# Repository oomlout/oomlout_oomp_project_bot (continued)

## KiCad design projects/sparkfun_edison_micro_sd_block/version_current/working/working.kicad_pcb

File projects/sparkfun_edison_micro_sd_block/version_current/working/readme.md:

# Edison_Micro_SD_Block by sparkfun  
This is a harvested standardized copy of a project from github.  
The original project can be found at:  
https://github.com/sparkfun/Edison_Micro_SD_Block  
Please consult that link for additional, details, files, and license information.  
Note: It was auto harvested and if the original repo had more than one board file or anything out of the ordinary the files here are likely not representative.

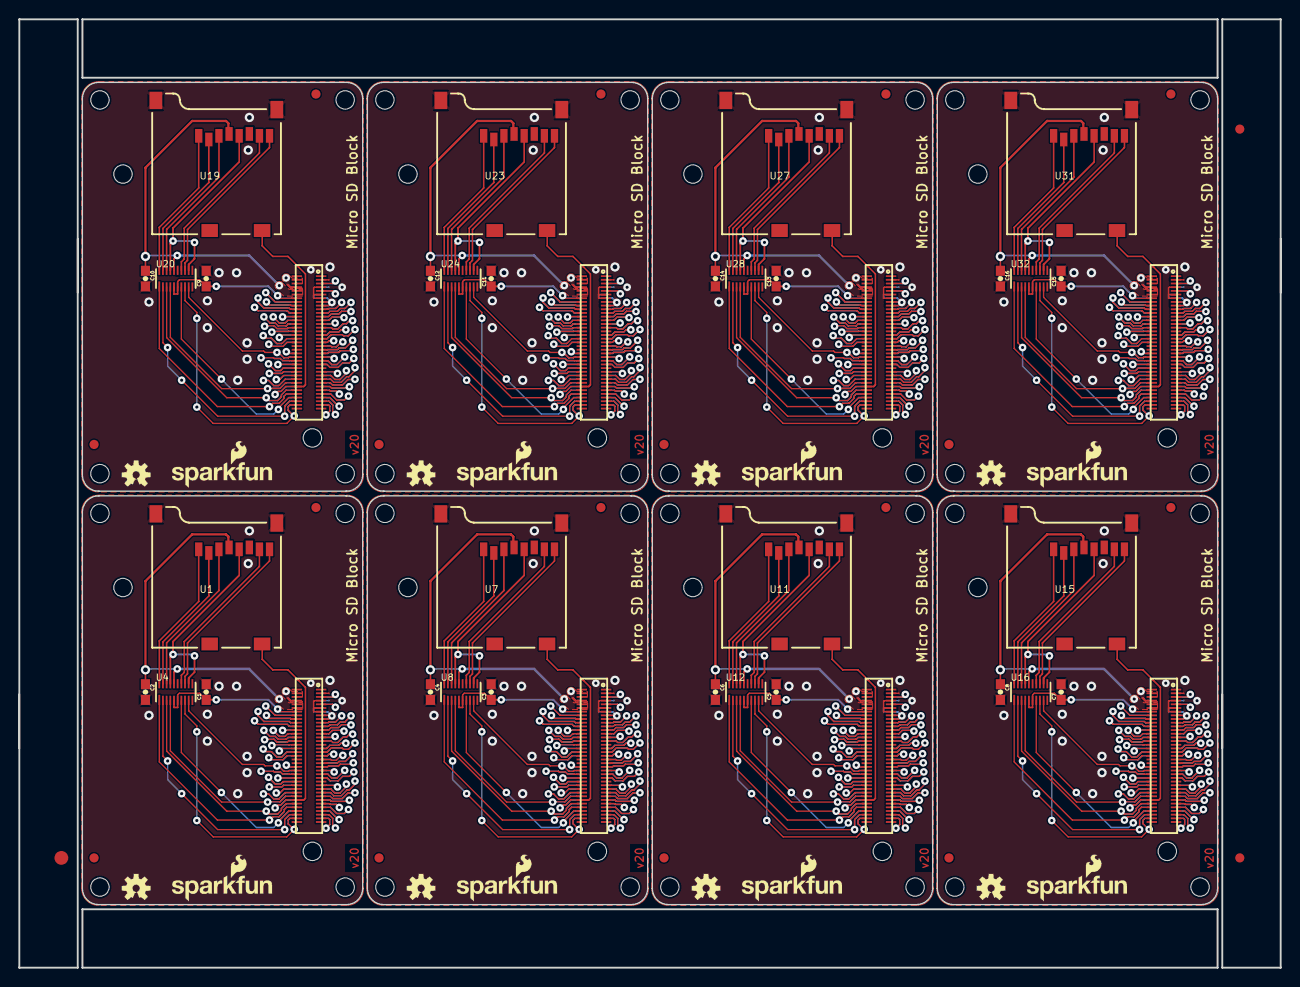
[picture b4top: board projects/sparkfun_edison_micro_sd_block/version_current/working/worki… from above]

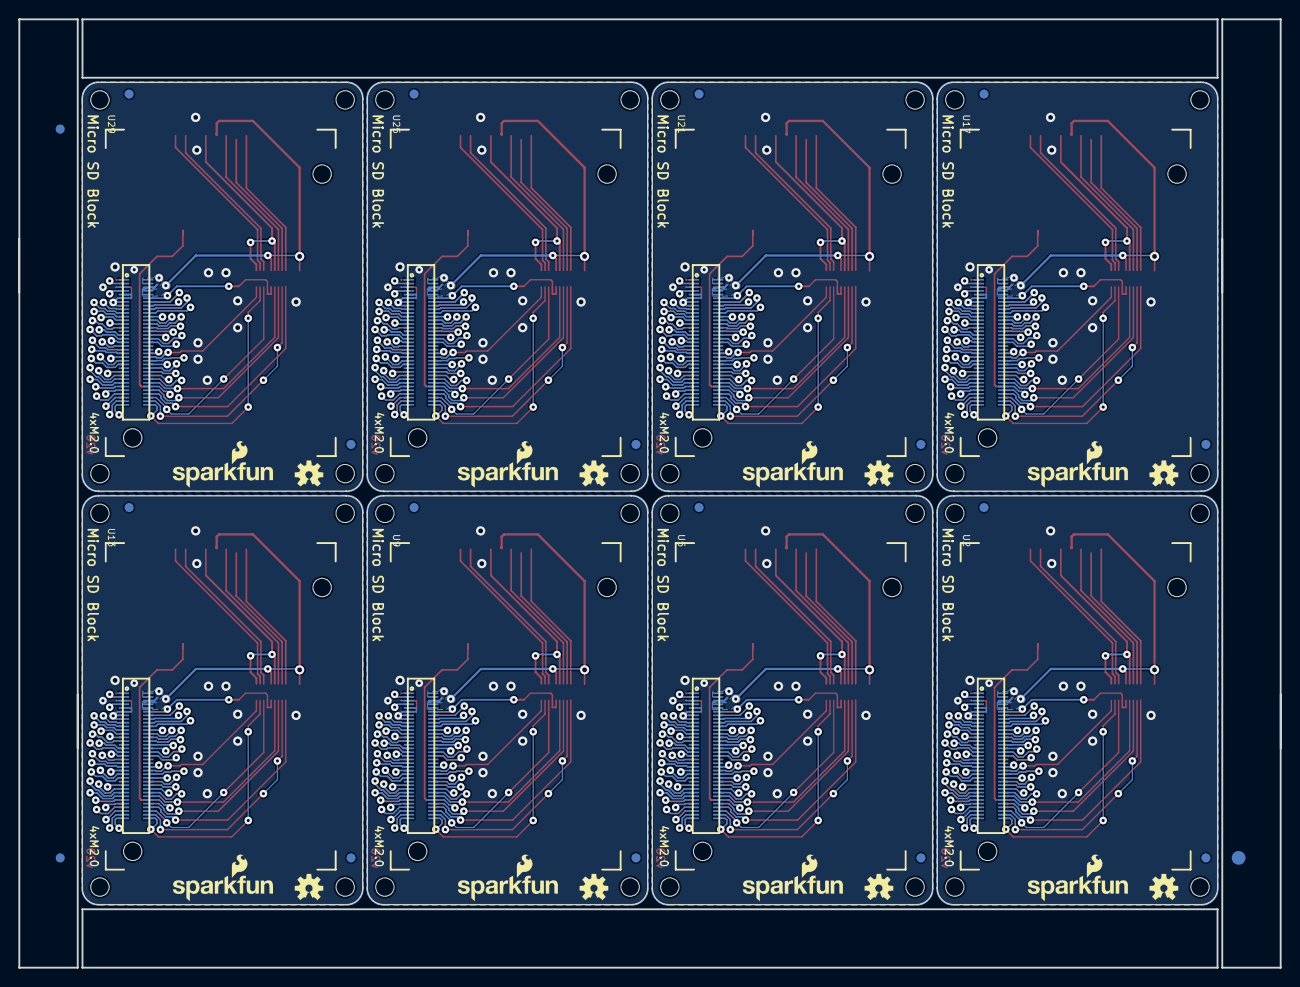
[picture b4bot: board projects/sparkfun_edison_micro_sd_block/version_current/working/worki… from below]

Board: 4 copper layers, 137.2 x 103.1 mm, 150 parts (51 on the bottom side), 512 nets.

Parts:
@HOLE0, @HOLE1, @HOLE2, @HOLE3, @HOLE4, @HOLE5, @HOLE6, @HOLE7, @HOLE8, @HOLE9, @HOLE10, @HOLE11, @HOLE12, @HOLE13, @HOLE14, @HOLE15, @HOLE16, @HOLE17, @HOLE18, @HOLE19, @HOLE20, @HOLE21, @HOLE22, @HOLE23, @HOLE24, @HOLE25, @HOLE26, @HOLE27, @HOLE28, @HOLE29, @HOLE30, @HOLE31: (no value)
C1, C2, C3, C4, C5, C6, C7, C8, C9, C10, C11, C12, C13, C14, C15, C16: 0.1uF; 0603-CAP
E$1, E$2: FIDUCIAL-1.5X3
E$3, E$4, E$5, E$6: FIDUCIAL-1X2
FID1, FID2, FID3, FID4, FID5, FID6, FID7, FID8, FID9, FID10, FID11, FID12, FID13, FID14, FID15, FID16, FID17, FID18, FID19, FID20, FID21, FID22, FID23, FID24, FID25, FID26, FID27, FID28, FID29, FID30, FID31, FID32: FIDUCIAL1X2; FIDUCIAL-1X2
LOGO1, LOGO2, LOGO5, LOGO7, LOGO9, LOGO11, LOGO13, LOGO15, LOGO17, LOGO19, LOGO21, LOGO23, LOGO25, LOGO27, LOGO29, LOGO31: OSHW-LOGOS; OSHW-LOGO-S
LOGO3, LOGO4, LOGO6, LOGO8, LOGO10, LOGO12, LOGO14, LOGO16, LOGO18, LOGO20, LOGO22, LOGO24, LOGO26, LOGO28, LOGO30, LOGO32: SFE_LOGO_NAME_FLAME.1_INCH; SFE_LOGO_NAME_FLAME_.1
U1, U7, U11, U15, U19, U23, U27, U31: USD-SOCKETNEW; MICRO-SD-SOCKET-PP
U2, U5, U9, U13, U17, U21, U25, U29: EDISON_CONNECTOR_FULLMOUNTING_HOLES; EDISON_DAUGHTER
U3, U6, U10, U14, U18, U22, U26, U30: EDISON_CONNECTOR_FULLHEADER; DF40C-70DP-0.4(51)
U4, U8, U12, U16, U20, U24, U28, U32: TXB0108; UFDFN-20

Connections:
1.8V: C1.1, U2.12, U3.12, U4.P$5, U4.P$6
1.8V1: C3.1, U5.12, U6.12, U8.P$5, U8.P$6
1.8V2: C5.1, U9.12, U10.12, U12.P$5, U12.P$6
1.8V3: C7.1, U13.12, U14.12, U16.P$5, U16.P$6
1.8V4: C9.1, U17.12, U18.12, U20.P$5, U20.P$6
1.8V5: C11.1, U21.12, U22.12, U24.P$5, U24.P$6
1.8V6: C13.1, U25.12, U26.12, U28.P$5, U28.P$6
1.8V7: C15.1, U29.12, U30.12, U32.P$5, U32.P$6
3.3V: C2.1, U1.4, U2.8, U2.10, U3.8, U3.10, U4.P$16
3.3V1: C4.1, U5.8, U5.10, U6.8, U6.10, U7.4, U8.P$16
3.3V2: C6.1, U9.8, U9.10, U10.8, U10.10, U11.4, U12.P$16
3.3V3: C8.1, U13.8, U13.10, U14.8, U14.10, U15.4, U16.P$16
3.3V4: C10.1, U17.8, U17.10, U18.8, U18.10, U19.4, U20.P$16
3.3V5: C12.1, U21.8, U21.10, U22.8, U22.10, U23.4, U24.P$16
3.3V6: C14.1, U25.8, U25.10, U26.8, U26.10, U27.4, U28.P$16
3.3V7: C16.1, U29.8, U29.10, U30.8, U30.10, U31.4, U32.P$16
DCIN: U2.14, U3.14
DCIN1: U5.14, U6.14
DCIN2: U9.14, U10.14
DCIN3: U13.14, U14.14
DCIN4: U17.14, U18.14
DCIN5: U21.14, U22.14
DCIN6: U25.14, U26.14
DCIN7: U29.14, U30.14
FAULT: U2.19, U3.19
FAULT1: U5.19, U6.19
FAULT2: U9.19, U10.19
FAULT3: U13.19, U14.19
FAULT4: U17.19, U18.19
FAULT5: U21.19, U22.19
FAULT6: U25.19, U26.19
FAULT7: U29.19, U30.19
FW_RCVR: U2.69, U3.69
FW_RCVR1: U5.69, U6.69
FW_RCVR2: U9.69, U10.69
FW_RCVR3: U13.69, U14.69
FW_RCVR4: U17.69, U18.69
FW_RCVR5: U21.69, U22.69
FW_RCVR6: U25.69, U26.69
FW_RCVR7: U29.69, U30.69
GND: C1.2, C2.2, U1.6, U1.GND1, U1.GND3, U2.1, U2.5, U2.9, U2.11, U2.13, U2.15, U3.1, U3.5, U3.9, U3.11, U3.13, U3.15, U4.P$15
GND1: C3.2, C4.2, U5.1, U5.5, U5.9, U5.11, U5.13, U5.15, U6.1, U6.5, U6.9, U6.11, U6.13, U6.15, U7.6, U7.GND1, U7.GND3, U8.P$15
GND2: C5.2, C6.2, U9.1, U9.5, U9.9, U9.11, U9.13, U9.15, U10.1, U10.5, U10.9, U10.11, U10.13, U10.15, U11.6, U11.GND1, U11.GND3, U12.P$15
GND3: C7.2, C8.2, U13.1, U13.5, U13.9, U13.11, U13.13, U13.15, U14.1, U14.5, U14.9, U14.11, U14.13, U14.15, U15.6, U15.GND1, U15.GND3, U16.P$15
GND4: C9.2, C10.2, U17.1, U17.5, U17.9, U17.11, U17.13, U17.15, U18.1, U18.5, U18.9, U18.11, U18.13, U18.15, U19.6, U19.GND1, U19.GND3, U20.P$15
GND5: C11.2, C12.2, U21.1, U21.5, U21.9, U21.11, U21.13, U21.15, U22.1, U22.5, U22.9, U22.11, U22.13, U22.15, U23.6, U23.GND1, U23.GND3, U24.P$15
GND6: C13.2, C14.2, U25.1, U25.5, U25.9, U25.11, U25.13, U25.15, U26.1, U26.5, U26.9, U26.11, U26.13, U26.15, U27.6, U27.GND1, U27.GND3, U28.P$15
GND7: C15.2, C16.2, U29.1, U29.5, U29.9, U29.11, U29.13, U29.15, U30.1, U30.5, U30.9, U30.11, U30.13, U30.15, U31.6, U31.GND1, U31.GND3, U32.P$15
GP1: U5.48, U6.48
GP2: U5.42, U6.42
GP3: U5.34, U6.34
GP4: U5.32, U6.32
GP5: U5.30, U6.30
GP6: U5.28, U6.28
GP7: U5.26, U6.26
GP8: U5.25, U6.25
GP9: U5.24, U6.24
GP10: U9.48, U10.48
GP11: U9.42, U10.42
GP12: U9.34, U10.34
GP12_PWM0: U2.35, U3.35
GP12_PWM1: U5.35, U6.35
GP12_PWM2: U9.35, U10.35
GP12_PWM3: U13.35, U14.35
GP12_PWM4: U17.35, U18.35
GP12_PWM5: U21.35, U22.35
GP12_PWM6: U25.35, U26.35
GP12_PWM7: U29.35, U30.35
GP13: U9.32, U10.32
GP13_PWM1: U2.33, U3.33
GP13_PWM2: U5.33, U6.33
GP13_PWM3: U9.33, U10.33
GP13_PWM4: U13.33, U14.33
GP13_PWM5: U17.33, U18.33
GP13_PWM6: U21.33, U22.33
GP13_PWM7: U25.33, U26.33
GP13_PWM8: U29.33, U30.33
GP14: U2.48, U3.48
GP15: U2.42, U3.42
GP16: U9.30, U10.30
GP17: U9.28, U10.28
GP18: U9.26, U10.26
GP19: U9.25, U10.25
GP19_I2C_1_SCL: U2.41, U3.41
GP19_I2C_1_SCL1: U5.41, U6.41
GP19_I2C_1_SCL2: U9.41, U10.41
GP19_I2C_1_SCL3: U13.41, U14.41
GP19_I2C_1_SCL4: U17.41, U18.41
GP19_I2C_1_SCL5: U21.41, U22.41
GP19_I2C_1_SCL6: U25.41, U26.41
GP19_I2C_1_SCL7: U29.41, U30.41
GP20: U9.24, U10.24
GP20_I2C_1_SDA: U2.43, U3.43
GP20_I2C_1_SDA1: U5.43, U6.43
GP20_I2C_1_SDA2: U9.43, U10.43
GP20_I2C_1_SDA3: U13.43, U14.43
GP20_I2C_1_SDA4: U17.43, U18.43
GP20_I2C_1_SDA5: U21.43, U22.43
GP20_I2C_1_SDA6: U25.43, U26.43
GP20_I2C_1_SDA7: U29.43, U30.43
GP21: U13.48, U14.48
GP22: U13.42, U14.42
GP23: U13.34, U14.34
GP24: U13.32, U14.32
GP25: U13.30, U14.30
GP26: U13.28, U14.28
GP27: U13.26, U14.26
GP27_I2C_6_SCL: U2.45, U3.45
GP27_I2C_6_SCL1: U5.45, U6.45
GP27_I2C_6_SCL2: U9.45, U10.45
GP27_I2C_6_SCL3: U13.45, U14.45
GP27_I2C_6_SCL4: U17.45, U18.45
GP27_I2C_6_SCL5: U21.45, U22.45
GP27_I2C_6_SCL6: U25.45, U26.45
GP27_I2C_6_SCL7: U29.45, U30.45
GP28: U13.25, U14.25
GP28_I2C_6_SDA: U2.47, U3.47
GP28_I2C_6_SDA1: U5.47, U6.47
GP28_I2C_6_SDA2: U9.47, U10.47
GP28_I2C_6_SDA3: U13.47, U14.47
GP28_I2C_6_SDA4: U17.47, U18.47
GP28_I2C_6_SDA5: U21.47, U22.47
GP28_I2C_6_SDA6: U25.47, U26.47
GP28_I2C_6_SDA7: U29.47, U30.47
GP29: U13.24, U14.24
GP30: U17.48, U18.48
GP31: U17.42, U18.42
GP32: U17.34, U18.34
GP33: U17.32, U18.32
GP34: U17.30, U18.30
GP35: U17.28, U18.28
GP36: U17.26, U18.26
GP37: U17.25, U18.25
GP38: U17.24, U18.24
GP39: U21.48, U22.48
GP40: U21.42, U22.42
GP40_I2S_2_CLK: U2.52, U3.52
GP40_I2S_2_CLK1: U5.52, U6.52
GP40_I2S_2_CLK2: U9.52, U10.52
GP40_I2S_2_CLK3: U13.52, U14.52
GP40_I2S_2_CLK4: U17.52, U18.52
GP40_I2S_2_CLK5: U21.52, U22.52
GP40_I2S_2_CLK6: U25.52, U26.52
GP40_I2S_2_CLK7: U29.52, U30.52
GP41: U21.34, U22.34
GP41_I2S_2_FS: U2.54, U3.54
GP41_I2S_2_FS1: U5.54, U6.54
GP41_I2S_2_FS2: U9.54, U10.54
GP41_I2S_2_FS3: U13.54, U14.54
GP41_I2S_2_FS4: U17.54, U18.54
GP41_I2S_2_FS5: U21.54, U22.54
GP41_I2S_2_FS6: U25.54, U26.54
GP41_I2S_2_FS7: U29.54, U30.54
GP42: U21.32, U22.32
GP42_I2S_2_RXD: U2.50, U3.50
GP42_I2S_2_RXD1: U5.50, U6.50
GP42_I2S_2_RXD2: U9.50, U10.50
GP42_I2S_2_RXD3: U13.50, U14.50
GP42_I2S_2_RXD4: U17.50, U18.50
GP42_I2S_2_RXD5: U21.50, U22.50
GP42_I2S_2_RXD6: U25.50, U26.50
GP42_I2S_2_RXD7: U29.50, U30.50
GP43: U21.30, U22.30
GP43_I2S_2_TXD: U2.56, U3.56
GP43_I2S_2_TXD1: U5.56, U6.56
GP43_I2S_2_TXD2: U9.56, U10.56
GP43_I2S_2_TXD3: U13.56, U14.56
GP43_I2S_2_TXD4: U17.56, U18.56
GP43_I2S_2_TXD5: U21.56, U22.56
GP43_I2S_2_TXD6: U25.56, U26.56
GP43_I2S_2_TXD7: U29.56, U30.56
GP44: U2.24, U3.24
GP45: U2.26, U3.26
GP46: U2.28, U3.28
GP47: U2.30, U3.30
GP48: U2.32, U3.32
GP49: U2.34, U3.34
GP50: U21.28, U22.28
GP51: U21.26, U22.26
GP52: U21.25, U22.25
GP53: U21.24, U22.24
GP54: U25.48, U26.48
GP55: U25.42, U26.42
GP56: U25.34, U26.34
GP57: U25.32, U26.32
GP58: U25.30, U26.30
GP59: U25.28, U26.28
GP60: U25.26, U26.26
GP61: U25.25, U26.25
GP62: U25.24, U26.24
GP63: U29.48, U30.48
GP64: U29.42, U30.42
GP65: U29.34, U30.34
GP66: U29.32, U30.32
GP67: U29.30, U30.30
GP68: U29.28, U30.28
GP69: U29.26, U30.26
GP70: U29.25, U30.25
GP71: U29.24, U30.24
GP77_SD_0_CD#: U1.CD1, U2.60, U3.60
GP77_SD_0_CD#1: U5.60, U6.60, U7.CD1
GP77_SD_0_CD#2: U9.60, U10.60, U11.CD1
GP77_SD_0_CD#3: U13.60, U14.60, U15.CD1
GP77_SD_0_CD#4: U17.60, U18.60, U19.CD1
GP77_SD_0_CD#5: U21.60, U22.60, U23.CD1
GP77_SD_0_CD#6: U25.60, U26.60, U27.CD1
GP77_SD_0_CD#7: U29.60, U30.60, U31.CD1
GP78_SD_0_CLK: U2.58, U3.58, U4.P$4
GP78_SD_0_CLK1: U5.58, U6.58, U8.P$4
GP78_SD_0_CLK2: U9.58, U10.58, U12.P$4
GP78_SD_0_CLK3: U13.58, U14.58, U16.P$4
GP78_SD_0_CLK4: U17.58, U18.58, U20.P$4
GP78_SD_0_CLK5: U21.58, U22.58, U24.P$4
GP78_SD_0_CLK6: U25.58, U26.58, U28.P$4
GP78_SD_0_CLK7: U29.58, U30.58, U32.P$4
GP79_SD_0_CMD: U2.62, U3.62, U4.P$3
GP79_SD_0_CMD1: U5.62, U6.62, U8.P$3
GP79_SD_0_CMD2: U9.62, U10.62, U12.P$3
GP79_SD_0_CMD3: U13.62, U14.62, U16.P$3
GP79_SD_0_CMD4: U17.62, U18.62, U20.P$3
GP79_SD_0_CMD5: U21.62, U22.62, U24.P$3
GP79_SD_0_CMD6: U25.62, U26.62, U28.P$3
GP79_SD_0_CMD7: U29.62, U30.62, U32.P$3
GP80_SD_0_DAT0: U2.66, U3.66, U4.P$7
GP80_SD_0_DAT1: U5.66, U6.66, U8.P$7
GP80_SD_0_DAT2: U9.66, U10.66, U12.P$7
GP80_SD_0_DAT3: U13.66, U14.66, U16.P$7
GP80_SD_0_DAT4: U17.66, U18.66, U20.P$7
GP80_SD_0_DAT5: U21.66, U22.66, U24.P$7
GP80_SD_0_DAT6: U25.66, U26.66, U28.P$7
GP80_SD_0_DAT7: U29.66, U30.66, U32.P$7
GP81_SD_0_DAT1: U2.70, U3.70, U4.P$8
GP81_SD_0_DAT2: U5.70, U6.70, U8.P$8
GP81_SD_0_DAT3: U9.70, U10.70, U12.P$8
GP81_SD_0_DAT4: U13.70, U14.70, U16.P$8
GP81_SD_0_DAT5: U17.70, U18.70, U20.P$8
GP81_SD_0_DAT6: U21.70, U22.70, U24.P$8
GP81_SD_0_DAT7: U25.70, U26.70, U28.P$8
GP81_SD_0_DAT8: U29.70, U30.70, U32.P$8
GP82_SD_0_DAT1: U5.64, U6.64, U8.P$1
GP82_SD_0_DAT2: U2.64, U3.64, U4.P$1
GP82_SD_0_DAT3: U9.64, U10.64, U12.P$1
GP82_SD_0_DAT4: U13.64, U14.64, U16.P$1
GP82_SD_0_DAT5: U17.64, U18.64, U20.P$1
GP82_SD_0_DAT6: U21.64, U22.64, U24.P$1
GP82_SD_0_DAT7: U25.64, U26.64, U28.P$1
GP82_SD_0_DAT8: U29.64, U30.64, U32.P$1
GP83_SD_0_DAT1: U5.68, U6.68, U8.P$2
GP83_SD_0_DAT2: U9.68, U10.68, U12.P$2
GP83_SD_0_DAT3: U2.68, U3.68, U4.P$2
GP83_SD_0_DAT4: U13.68, U14.68, U16.P$2
GP83_SD_0_DAT5: U17.68, U18.68, U20.P$2
GP83_SD_0_DAT6: U21.68, U22.68, U24.P$2
GP83_SD_0_DAT7: U25.68, U26.68, U28.P$2
GP83_SD_0_DAT8: U29.68, U30.68, U32.P$2
GP84_SD_CLK_FB: U2.44, U3.44, U4.P$9
GP84_SD_CLK_FB1: U5.44, U6.44, U8.P$9
GP84_SD_CLK_FB2: U9.44, U10.44, U12.P$9
GP84_SD_CLK_FB3: U13.44, U14.44, U16.P$9
GP84_SD_CLK_FB4: U17.44, U18.44, U20.P$9
GP84_SD_CLK_FB5: U21.44, U22.44, U24.P$9
GP84_SD_CLK_FB6: U25.44, U26.44, U28.P$9
GP84_SD_CLK_FB7: U29.44, U30.44, U32.P$9
GP109_SPI_2_CLK: U2.55, U3.55
GP109_SPI_2_CLK1: U5.55, U6.55
GP109_SPI_2_CLK2: U9.55, U10.55
GP109_SPI_2_CLK3: U13.55, U14.55
GP109_SPI_2_CLK4: U17.55, U18.55
GP109_SPI_2_CLK5: U21.55, U22.55
GP109_SPI_2_CLK6: U25.55, U26.55
GP109_SPI_2_CLK7: U29.55, U30.55
GP110_SPI_2_FS0: U2.53, U3.53
GP110_SPI_2_FS1: U5.53, U6.53
GP110_SPI_2_FS2: U9.53, U10.53
GP110_SPI_2_FS3: U13.53, U14.53
GP110_SPI_2_FS4: U17.53, U18.53
GP110_SPI_2_FS5: U21.53, U22.53
GP110_SPI_2_FS6: U25.53, U26.53
GP110_SPI_2_FS7: U29.53, U30.53
GP111_SPI_2_FS1: U2.51, U3.51
GP111_SPI_2_FS2: U5.51, U6.51
GP111_SPI_2_FS3: U9.51, U10.51
GP111_SPI_2_FS4: U13.51, U14.51
GP111_SPI_2_FS5: U17.51, U18.51
GP111_SPI_2_FS6: U21.51, U22.51
GP111_SPI_2_FS7: U25.51, U26.51
GP111_SPI_2_FS8: U29.51, U30.51
GP114_SPI_2_RXD: U2.59, U3.59
GP114_SPI_2_RXD1: U5.59, U6.59
GP114_SPI_2_RXD2: U9.59, U10.59
GP114_SPI_2_RXD3: U13.59, U14.59
GP114_SPI_2_RXD4: U17.59, U18.59
GP114_SPI_2_RXD5: U21.59, U22.59
GP114_SPI_2_RXD6: U25.59, U26.59
GP114_SPI_2_RXD7: U29.59, U30.59
GP115_SPI_2_TXD: U2.57, U3.57
GP115_SPI_2_TXD1: U5.57, U6.57
GP115_SPI_2_TXD2: U9.57, U10.57
GP115_SPI_2_TXD3: U13.57, U14.57
GP115_SPI_2_TXD4: U17.57, U18.57
GP115_SPI_2_TXD5: U21.57, U22.57
GP115_SPI_2_TXD6: U25.57, U26.57
GP115_SPI_2_TXD7: U29.57, U30.57
GP128_UART_1_CTS: U2.65, U3.65
GP128_UART_1_CTS1: U5.65, U6.65
GP128_UART_1_CTS2: U9.65, U10.65
GP128_UART_1_CTS3: U13.65, U14.65
GP128_UART_1_CTS4: U17.65, U18.65
GP128_UART_1_CTS5: U21.65, U22.65
GP128_UART_1_CTS6: U25.65, U26.65
GP128_UART_1_CTS7: U29.65, U30.65
GP129_UART_1_RTS: U2.63, U3.63
GP129_UART_1_RTS1: U5.63, U6.63
GP129_UART_1_RTS2: U9.63, U10.63
GP129_UART_1_RTS3: U13.63, U14.63
GP129_UART_1_RTS4: U17.63, U18.63
GP129_UART_1_RTS5: U21.63, U22.63
GP129_UART_1_RTS6: U25.63, U26.63
GP129_UART_1_RTS7: U29.63, U30.63
GP130_UART_1_RX: U2.61, U3.61
GP130_UART_1_RX1: U5.61, U6.61
GP130_UART_1_RX2: U9.61, U10.61
GP130_UART_1_RX3: U13.61, U14.61
GP130_UART_1_RX4: U17.61, U18.61
GP130_UART_1_RX5: U21.61, U22.61
GP130_UART_1_RX6: U25.61, U26.61
GP130_UART_1_RX7: U29.61, U30.61
GP131_UART_1_TX: U2.46, U3.46
GP131_UART_1_TX1: U5.46, U6.46
GP131_UART_1_TX2: U9.46, U10.46
GP131_UART_1_TX3: U13.46, U14.46
GP131_UART_1_TX4: U17.46, U18.46
GP131_UART_1_TX5: U21.46, U22.46
GP131_UART_1_TX6: U25.46, U26.46
GP131_UART_1_TX7: U29.46, U30.46
GP134_UART_2_RX: U2.22, U3.22
GP134_UART_2_RX1: U5.22, U6.22
GP134_UART_2_RX2: U9.22, U10.22
GP134_UART_2_RX3: U13.22, U14.22
GP134_UART_2_RX4: U17.22, U18.22
GP134_UART_2_RX5: U21.22, U22.22
GP134_UART_2_RX6: U25.22, U26.22
GP134_UART_2_RX7: U29.22, U30.22
GP135_UART_2_TX: U2.27, U3.27
GP135_UART_2_TX1: U5.27, U6.27
GP135_UART_2_TX2: U9.27, U10.27
GP135_UART_2_TX3: U13.27, U14.27
GP135_UART_2_TX4: U17.27, U18.27
GP135_UART_2_TX5: U21.27, U22.27
GP135_UART_2_TX6: U25.27, U26.27
GP135_UART_2_TX7: U29.27, U30.27
GP165: U2.25, U3.25
GP182_PWM1: U5.37, U6.37
GP182_PWM2: U2.37, U3.37
GP182_PWM3: U9.37, U10.37
GP182_PWM4: U13.37, U14.37
GP182_PWM5: U17.37, U18.37
GP182_PWM6: U21.37, U22.37
GP182_PWM7: U25.37, U26.37
GP182_PWM8: U29.37, U30.37
GP183_PWM1: U5.39, U6.39
GP183_PWM2: U9.39, U10.39
GP183_PWM3: U2.39, U3.39
GP183_PWM4: U13.39, U14.39
GP183_PWM5: U17.39, U18.39
GP183_PWM6: U21.39, U22.39
GP183_PWM7: U25.39, U26.39
GP183_PWM8: U29.39, U30.39
MSIC_SLP_CLK: U2.7, U3.7
MSIC_SLP_CLK1: U5.7, U6.7
MSIC_SLP_CLK2: U9.7, U10.7
MSIC_SLP_CLK3: U13.7, U14.7
MSIC_SLP_CLK4: U17.7, U18.7
MSIC_SLP_CLK5: U21.7, U22.7
MSIC_SLP_CLK6: U25.7, U26.7
MSIC_SLP_CLK7: U29.7, U30.7
unnamed: U1.1, U4.P$20
unnamed: U1.2, U4.P$19
unnamed: U1.3, U4.P$18
unnamed: U7.1, U8.P$20
unnamed: U1.7, U4.P$14
unnamed: U1.8, U4.P$13
unnamed: U7.2, U8.P$19
unnamed: U7.3, U8.P$18
unnamed: U7.7, U8.P$14
unnamed: U7.8, U8.P$13
unnamed: U11.1, U12.P$20
unnamed: U11.2, U12.P$19
unnamed: U11.3, U12.P$18
unnamed: U11.7, U12.P$14
unnamed: U11.8, U12.P$13
unnamed: U15.1, U16.P$20
unnamed: U15.2, U16.P$19
unnamed: U15.3, U16.P$18
unnamed: U15.7, U16.P$14
unnamed: U15.8, U16.P$13
unnamed: U19.1, U20.P$20
unnamed: U19.2, U20.P$19
unnamed: U19.3, U20.P$18
unnamed: U19.7, U20.P$14
unnamed: U19.8, U20.P$13
unnamed: U23.1, U24.P$20
unnamed: U23.2, U24.P$19
unnamed: U23.3, U24.P$18
unnamed: U23.7, U24.P$14
unnamed: U23.8, U24.P$13
unnamed: U27.1, U28.P$20
unnamed: U27.2, U28.P$19
unnamed: U27.3, U28.P$18
unnamed: U27.7, U28.P$14
unnamed: U27.8, U28.P$13
unnamed: U31.1, U32.P$20
unnamed: U31.2, U32.P$19
unnamed: U31.3, U32.P$18
unnamed: U31.7, U32.P$14
unnamed: U31.8, U32.P$13
OSC_CLK_OUT: U2.67, U3.67
OSC_CLK_OUT1: U5.67, U6.67
OSC_CLK_OUT2: U9.67, U10.67
OSC_CLK_OUT3: U13.67, U14.67
OSC_CLK_OUT4: U17.67, U18.67
OSC_CLK_OUT5: U21.67, U22.67
OSC_CLK_OUT6: U25.67, U26.67
OSC_CLK_OUT7: U29.67, U30.67
PSW: U2.21, U3.21
PSW1: U5.21, U6.21
PSW2: U9.21, U10.21
PSW3: U13.21, U14.21
PSW4: U17.21, U18.21
PSW5: U21.21, U22.21
PSW6: U25.21, U26.21
PSW7: U29.21, U30.21
PWRBTN#: U2.17, U3.17
PWRBTN#1: U5.17, U6.17
PWRBTN#2: U9.17, U10.17
PWRBTN#3: U13.17, U14.17
PWRBTN#4: U17.17, U18.17
PWRBTN#5: U21.17, U22.17
PWRBTN#6: U25.17, U26.17
PWRBTN#7: U29.17, U30.17
RCVR_MODE: U2.31, U3.31
RCVR_MODE1: U5.31, U6.31
RCVR_MODE2: U9.31, U10.31
RCVR_MODE3: U13.31, U14.31
RCVR_MODE4: U17.31, U18.31
RCVR_MODE5: U21.31, U22.31
RCVR_MODE6: U25.31, U26.31
RCVR_MODE7: U29.31, U30.31
RESET_OUT#: U2.36, U3.36
RESET_OUT#1: U5.36, U6.36
RESET_OUT#2: U9.36, U10.36
RESET_OUT#3: U13.36, U14.36
RESET_OUT#4: U17.36, U18.36
RESET_OUT#5: U21.36, U22.36
RESET_OUT#6: U25.36, U26.36
RESET_OUT#7: U29.36, U30.36
SCK: U1.5, U4.P$12, U4.P$17
SCK1: U7.5, U8.P$12, U8.P$17
SCK2: U11.5, U12.P$12, U12.P$17
SCK3: U15.5, U16.P$12, U16.P$17
SCK4: U19.5, U20.P$12, U20.P$17
SCK5: U23.5, U24.P$12, U24.P$17
SCK6: U27.5, U28.P$12, U28.P$17
SCK7: U31.5, U32.P$12, U32.P$17
USB_DN: U2.18, U3.18
USB_DN1: U5.18, U6.18
USB_DN2: U9.18, U10.18
USB_DN3: U13.18, U14.18
USB_DN4: U17.18, U18.18
USB_DN5: U21.18, U22.18
USB_DN6: U25.18, U26.18
USB_DN7: U29.18, U30.18
USB_DP: U2.16, U3.16
USB_DP1: U5.16, U6.16
USB_DP2: U9.16, U10.16
USB_DP3: U13.16, U14.16
USB_DP4: U17.16, U18.16
USB_DP5: U21.16, U22.16
USB_DP6: U25.16, U26.16
USB_DP7: U29.16, U30.16
USB_ID: U2.3, U3.3
USB_ID1: U5.3, U6.3
USB_ID2: U9.3, U10.3
USB_ID3: U13.3, U14.3
USB_ID4: U17.3, U18.3
USB_ID5: U21.3, U22.3
USB_ID6: U25.3, U26.3
USB_ID7: U29.3, U30.3
USB_VBUS: U2.20, U3.20
USB_VBUS1: U5.20, U6.20
USB_VBUS2: U9.20, U10.20
USB_VBUS3: U13.20, U14.20
USB_VBUS4: U17.20, U18.20
USB_VBUS5: U21.20, U22.20
USB_VBUS6: U25.20, U26.20
USB_VBUS7: U29.20, U30.20
VSYS: U2.2, U2.4, U2.6, U3.2, U3.4, U3.6
VSYS1: U5.2, U5.4, U5.6, U6.2, U6.4, U6.6
VSYS2: U9.2, U9.4, U9.6, U10.2, U10.4, U10.6
VSYS3: U13.2, U13.4, U13.6, U14.2, U14.4, U14.6
VSYS4: U17.2, U17.4, U17.6, U18.2, U18.4, U18.6
VSYS5: U21.2, U21.4, U21.6, U22.2, U22.4, U22.6
VSYS6: U25.2, U25.4, U25.6, U26.2, U26.4, U26.6
VSYS7: U29.2, U29.4, U29.6, U30.2, U30.4, U30.6
V_BAT_BKUP: U2.23, U3.23
V_BAT_BKUP1: U5.23, U6.23
V_BAT_BKUP2: U9.23, U10.23
V_BAT_BKUP3: U13.23, U14.23
V_BAT_BKUP4: U17.23, U18.23
V_BAT_BKUP5: U21.23, U22.23
V_BAT_BKUP6: U25.23, U26.23
V_BAT_BKUP7: U29.23, U30.23

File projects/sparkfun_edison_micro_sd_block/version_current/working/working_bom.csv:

"Id";"Designator";"Footprint";"Quantity";"Designation";"Supplier and ref";
1;"FID30,FID17,FID13,FID18,FID6,FID1,FID22,FID5,FID10,FID2,FID9,FID21,FID29,FID25,FID26,FID14,FID8,FID23,FID4,FID7,FID3,FID16,FID31,FID20,FID28,FID32,FID19,FID27,FID15,FID12,FID24,FID11";"FIDUCIAL-1X2";32;"FIDUCIAL1X2";;;
2;"@HOLE8,@HOLE30,@HOLE14,@HOLE17,@HOLE29,@HOLE7,@HOLE16,@HOLE13,@HOLE21,@HOLE3,@HOLE23,@HOLE31,@HOLE1,@HOLE10,@HOLE24,@HOLE26,@HOLE11,@HOLE18,@HOLE5,@HOLE25,@HOLE19,@HOLE6,@HOLE27,@HOLE12,@HOLE0,@HOLE22,@HOLE15,@HOLE2,@HOLE4,@HOLE20,@HOLE9,@HOLE28";"";32;"";;;
3;"U31,U11,U27,U1,U7,U19,U23,U15";"MICRO-SD-SOCKET-PP";8;"USD-SOCKETNEW";;;
4;"C10,C1,C11,C3,C9,C13,C12,C16,C15,C6,C7,C2,C4,C8,C14,C5";"0603-CAP";16;"0.1uF";;;
5;"LOGO31,LOGO23,LOGO1,LOGO27,LOGO15,LOGO19,LOGO11,LOGO7,LOGO13,LOGO9,LOGO17,LOGO5,LOGO25,LOGO21,LOGO2,LOGO29";"OSHW-LOGO-S";16;"OSHW-LOGOS";;;
6;"U24,U8,U20,U28,U16,U32,U12,U4";"UFDFN-20";8;"TXB0108";;;
7;"LOGO28,LOGO16,LOGO12,LOGO8,LOGO20,LOGO4,LOGO24,LOGO32,LOGO30,LOGO22,LOGO18,LOGO14,LOGO6,LOGO3,LOGO26,LOGO10";"SFE_LOGO_NAME_FLAME_.1";16;"SFE_LOGO_NAME_FLAME.1_INCH";;;
8;"E$1,E$2";"FIDUCIAL-1.5X3";2;"";;;
9;"E$5,E$4,E$3,E$6";"FIDUCIAL-1X2";4;"";;;
10;"U29,U21,U25,U17,U13,U5,U2,U9";"EDISON_DAUGHTER";8;"EDISON_CONNECTOR_FULLMOUNTING_HOLES";;;
11;"U10,U22,U3,U6,U18,U14,U26,U30";"DF40C-70DP-0.4(51)";8;"EDISON_CONNECTOR_FULLHEADER";;;
